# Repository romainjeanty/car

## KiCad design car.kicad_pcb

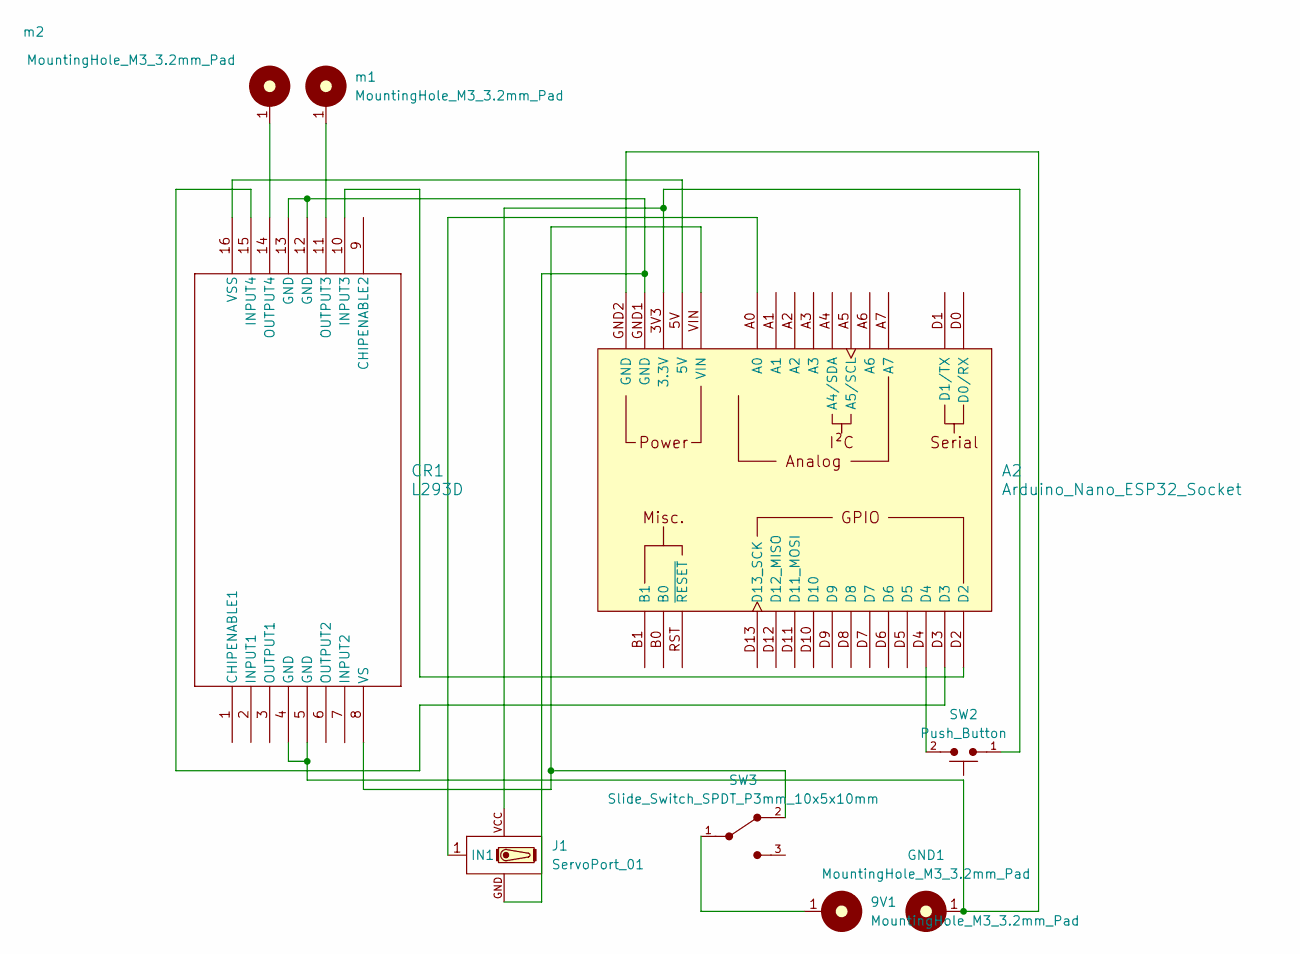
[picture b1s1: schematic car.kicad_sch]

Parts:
9V1: MountingHole_M3_3.2mm_Pad; MountingHole_3.2mm_Pad
A2: Arduino_Nano_ESP32_Socket
CR1: L293D; PowerDIP-16_STM
GND1: MountingHole_M3_3.2mm_Pad; MountingHole_3.2mm_Pad
J1: ServoPort_01; ServoPort_01_Vertical
SW2: Push_Button; SW_PUSH_6mm
SW3: Slide_Switch_SPDT_P3mm_10x5x10mm
m1, m2: MountingHole_M3_3.2mm_Pad; MountingHole_3.2mm_Pad

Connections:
unnamed: 9V1.1, SW3.1
unnamed: A2.3V3 (3.3V), J1.VCC, SW2.1
unnamed: A2.GND1 (GND), CR1.12 (GND), CR1.13 (GND), J1.GND
unnamed: A2.GND2 (GND), CR1.4 (GND), CR1.5 (GND), GND1.1
unnamed: A2.D4, SW2.2
unnamed: A2.D2, CR1.10 (INPUT3)
unnamed: A2.D3, CR1.15 (INPUT4)
unnamed: CR1.11 (OUTPUT3), m1.1
unnamed: CR1.14 (OUTPUT4), m2.1
unnamed: A2.VIN, CR1.8 (VS), SW3.2
unnamed: A2.5V, CR1.16 (VSS)
unnamed: A2.A0, J1.1 (IN1)

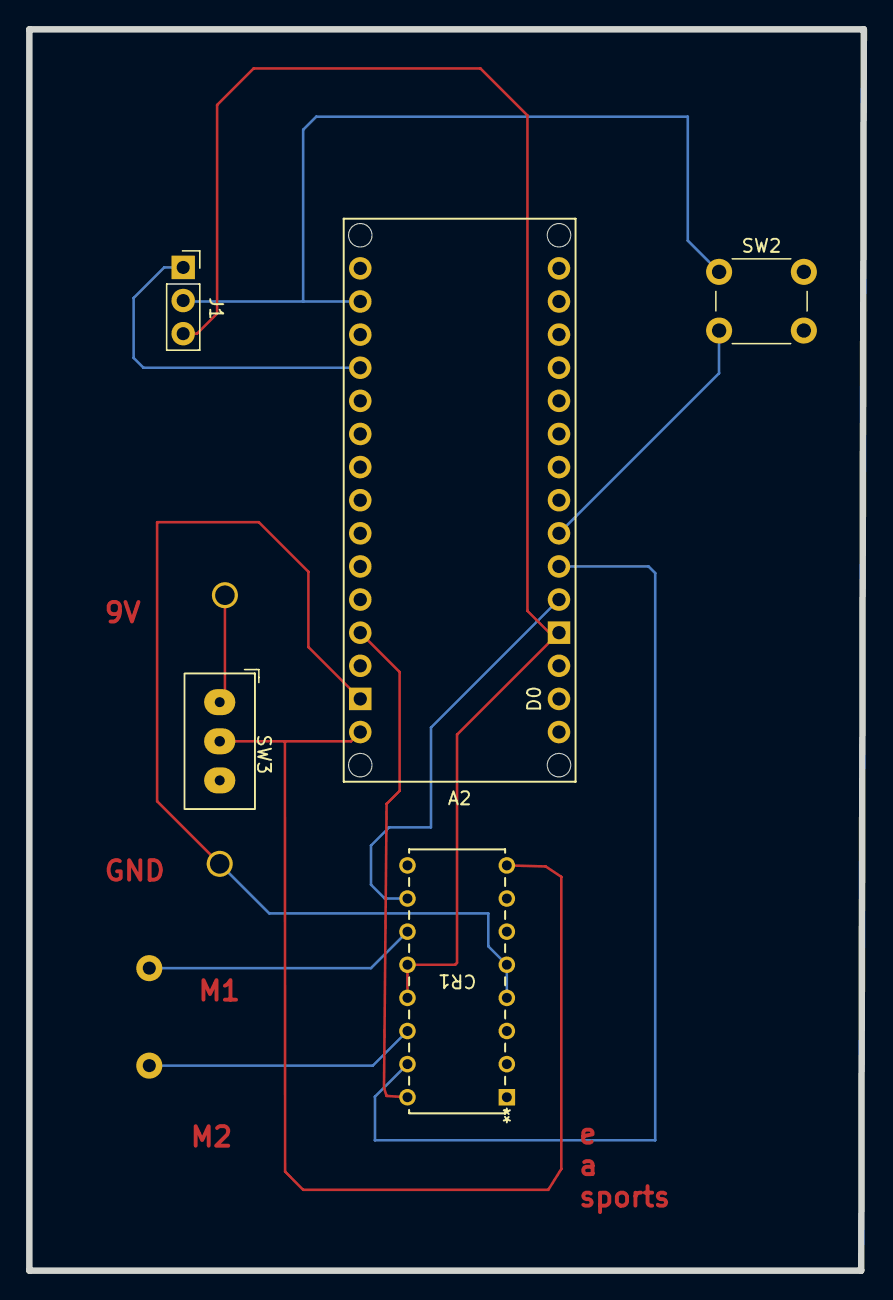
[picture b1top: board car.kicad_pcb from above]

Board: 2 copper layers, 64.0 x 95.2 mm, 9 parts (0 on the bottom side), 12 nets.

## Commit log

2025-05-08 car update
2025-05-13 add car
